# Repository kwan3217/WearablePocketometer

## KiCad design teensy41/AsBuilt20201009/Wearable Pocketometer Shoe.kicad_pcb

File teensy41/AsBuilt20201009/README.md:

Best-effort reconstruction of board as it existed on 2020-08-27 and 2020-10-09 when it was sent to the fab. 
This includes three kicad_pcb files which actually *are* the files that were on oshpark, as well as schematics
pulled from the tag on the old Kicad repository. Also including the KwanSystems.lib as it existed then. No
3D models or footprints -- the footprints are embedded in the kicad_pcb files, and the 3D models are
not needed for this purpose. Library copied from later version, as the library was not checked in. Since
they are just symbols, basically 'write once, ready many' data, it's fine that it's a later version.

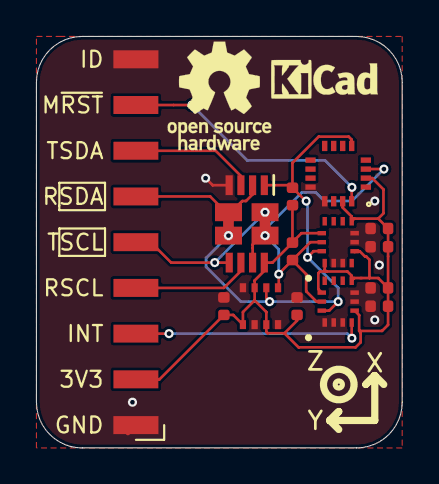
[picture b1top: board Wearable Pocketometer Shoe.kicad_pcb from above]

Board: 2 copper layers, 20.3 x 22.9 mm, 20 parts (1 on the bottom side), 10 nets.

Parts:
C1305, C1308, C1406, C1408, C1505, C1508: 100nF; C_0402_1005Metric
G501: DesignedWithKicad; Symbol_KiCAD-Logo_CopperAndSilkScreenTop_small
G502: KwanSystems; StKwansSoldermask
G503: OSHW; OSHW-Logo_5.7x6mm_SilkScreen
G904: Axis
J1201: Conn_01x09_Male; Harwin_M20-89009xx_1x09_P2.54mm_Horizontal
J1202, J1207: SolderJumper_2_Bridged; SolderJumper-2_Bridged
R1201, R1207: 10k; R_0402_1005Metric
U1201: AK09970
U1202: P82B96; TSSOP-8_3x3mm_P0.65mm
U1301, U1501: LSM6DSO; LGA-14L
U1401: BME280

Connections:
/Shoe/Q_3V3: C1305.1, C1308.1, C1406.1, C1408.2, C1505.1, C1508.1, J1201.2, R1201.1, R1207.1, U1201.2, U1201.15, U1202.8, U1301.5, U1301.8, U1301.12, U1401.2, U1401.6, U1401.8, U1501.1, U1501.5, U1501.8, U1501.12
/Shoe/Q_GND: C1305.2, C1308.2, C1406.2, C1408.1, C1505.2, C1508.2, J1201.1, J1201.9, U1201.12, U1201.13, U1202.4, U1301.1, U1301.2, U1301.3, U1301.6, U1301.7, U1401.1, U1401.5, U1401.7, U1501.2, U1501.3, U1501.6, U1501.7
/Shoe/Q_INT: J1201.3, U1301.4
/Shoe/Q_MAG~RST: J1201.8, U1201.16
/Shoe/Q_RX_SCL: J1201.4, U1202.6
/Shoe/Q_RX_SDA: J1201.6, J1202.2, U1202.2
/Shoe/Q_TX_SCL: J1201.5, J1207.2, U1202.5
/Shoe/Q_TX_SDA: J1201.7, U1202.3
/Shoe/SCL: J1207.1, R1207.2, U1201.3, U1202.7, U1301.13, U1401.4, U1501.13
/Shoe/SDA: J1202.1, R1201.2, U1201.5, U1202.1, U1301.14, U1401.3, U1501.14

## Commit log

2020-08-28 Adding WearablePocketometer as-ordered for Shoulder and Shoe boards
2020-08-28 Added Ponoko files
2020-10-15 Files used to build steel stencil and pocket board, 2020-Oct-09
2021-09-28 Renamed code to Teensy. Convention will be to not include WearablePocketometer in subfolders, but name of core harware/controller
2021-09-28 Renamed code to Teensy41.
2021-09-28 Re-cased folder for teensy41
2021-09-28 Added AsBuilt20201009
2021-09-28 Updated permissions
